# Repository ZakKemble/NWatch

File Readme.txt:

N|Watch - DIY Digital Wristwatch
http://blog.zakkemble.co.uk/diy-digital-wristwatch/

The firmware .hex and .eep files are compiled for ATmega328P

Fuses for ATmega328/328P
Internal RC 8MHz 6 CK/14CK + 65ms startup
Bootloader enabled, 256 words (512 bytes)
Serial program (SPI) enabled
Brown-out at 1.8V
High:		0xDE
Low:		0xE2
Extended:	0x06

./utils/bitmapConverter.exe
Utility to convert images (in ./imgs/) to pixel byte array

Font used for the large numbers on the main time display is AgencyFB Bold Wide available at http://www.fontsner.com/font/AgencyFBBoldWide-37966.html
My productions are published under GNU GPL v3 (see License.txt).

--------

Zak Kemble
contact@zakkemble.co.uk

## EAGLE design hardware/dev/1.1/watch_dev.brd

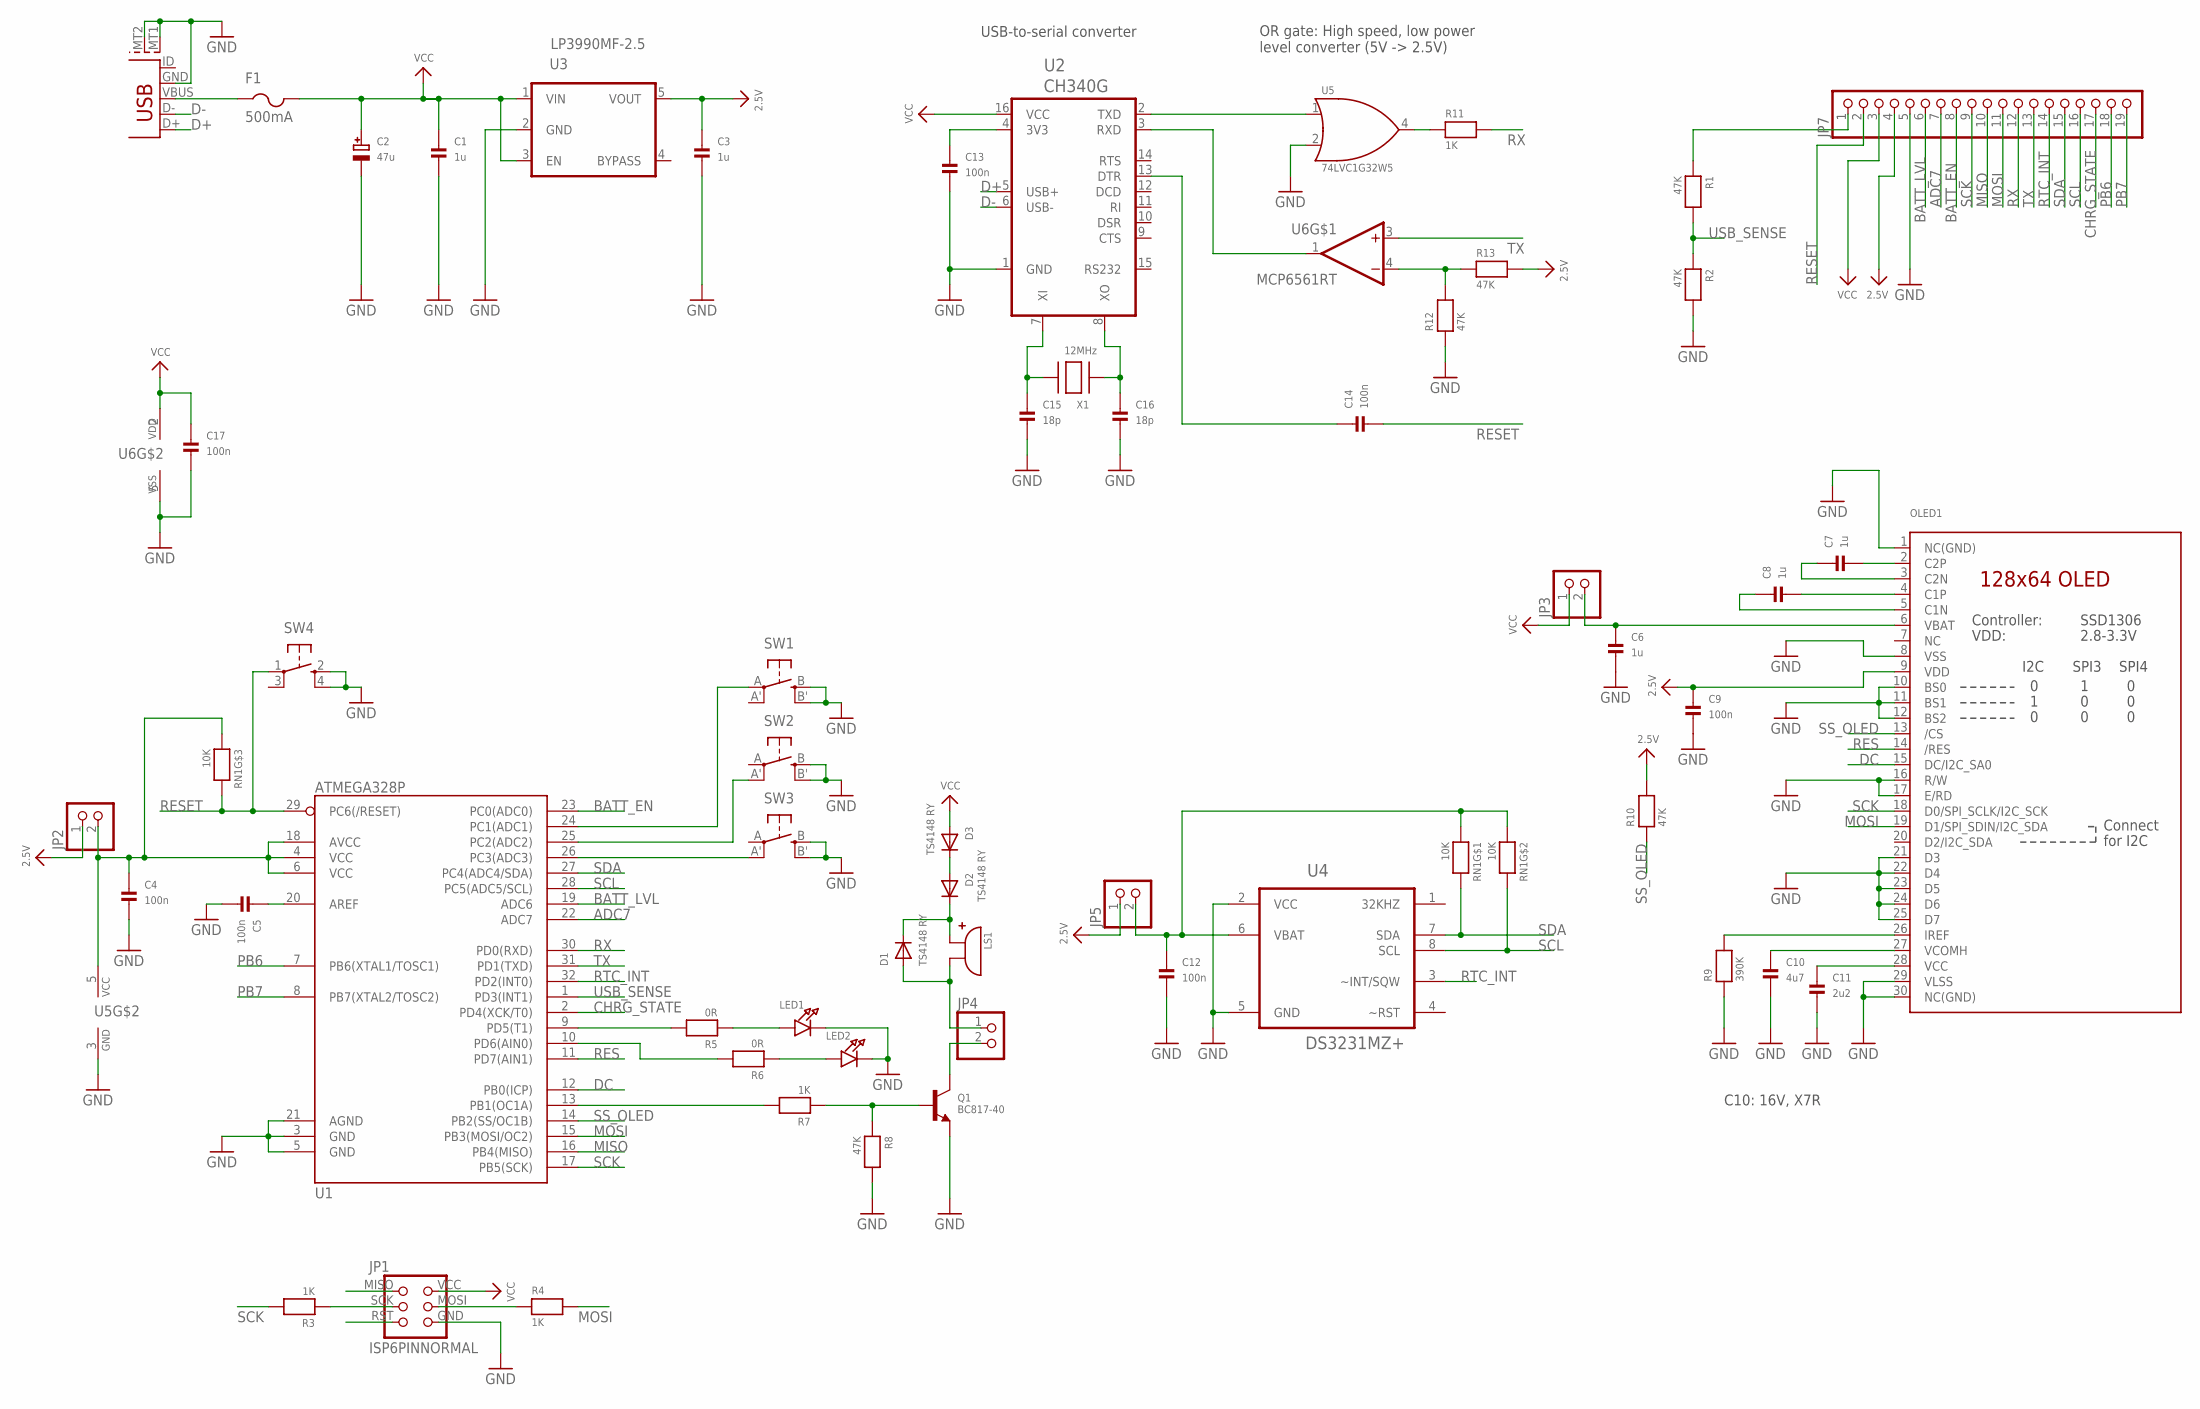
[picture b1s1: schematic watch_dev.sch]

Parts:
C1, C3, C6, C7, C8: 1u; 0805
C2: 47u; PANASONIC_C
C4, C5, C9, C12, C13, C14, C17: 100n; 0805
C10: 4u7; 0805
C11: 2u2; 0805
C15, C16: 18p; 0805
D1, D2, D3: TS4148 RY; 0805_DIODE
F1: 500mA; 1206
JP1: ISP6PINNORMAL; ISP6PIN
JP2, JP3, JP4, JP5: PINHD-1X2; 1X02
JP7: PINHD-1X19; 1X19
LED1, LED2: LED0805; CHIPLED_0805
LS1: ABMT-801-RC; PIEZO
OLED1: DISP_OLED_UG-2864HSWEG01_NOOUTLINE; UG-2864HSWEG01_1.3_WRAPAROUND
Q1: BC817-40; SOT23-WIDE
R1, R2, R8, R10, R12, R13: 47K; 0805
R3, R4, R7, R11: 1K; 0805
R5, R6: 0R; 0805
R9: 390K; 0805
RN1: 10K; RESPACK_4X0603
SW1, SW2, SW3: SPST_TACTMC32882; TACT_SMD4
SW4: SPST_TACTKMR2; KMR2
U1: ATMEGA328P; TQFP32-08
U2: CH340G; SOIC16_SMPAD
U3: LP3990MF-2.5; SOT95P275X110-5N
U4: DS3231MZ+; SOIC8_150MIL_SMPAD
U5: 74LVC1G32W5; SOT95P275X110-5N
U6: MCP6561RT; SOT95P275X110-5N
USB1: USB-MICROBLARGEPAD; USB-MICROB_LARGEPAD
X1: 12MHz; NX5032

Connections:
2.5V: C3.1, C9.1, JP2.1, JP5.1, JP7.4, OLED1.9 (VDD), R10.2, R13.2, U3.5 (VOUT)
ADC7: JP7.7, U1.22 (ADC7)
BATT_EN: JP7.8, U1.23 (PC0(ADC0))
BATT_LVL: JP7.6, U1.19 (ADC6)
CHRG_STATE: JP7.17, U1.2 (PD4(XCK/T0))
D+: U2.5 (USB+), USB1.D+
D-: U2.6 (USB-), USB1.D-
DC: OLED1.15 (DC/I2C_SA0), U1.12 (PB0(ICP))
GND: C1.2, C2.-, C3.2, C4.2, C5.2, C6.2, C9.2, C10.2, C11.2, C12.2, C13.2, C15.2, C16.2, C17.2, JP1.GND (6), JP7.5, LED1.C, LED2.C, OLED1.1 (NC(GND)), OLED1.8 (VSS), OLED1.10 (BS0), OLED1.11 (BS1), OLED1.12 (BS2), OLED1.16 (R/W), OLED1.17 (E/RD), OLED1.21 (D3), OLED1.22 (D4), OLED1.23 (D5), OLED1.24 (D6), OLED1.25 (D7), OLED1.29 (VLSS), OLED1.30 (NC(GND)), Q1.2 (E), R2.2, R8.2, R9.1, R12.1, SW1.B (S), SW1.B' (S1), SW2.B (S), SW2.B' (S1), SW3.B (S), SW3.B' (S1), SW4.2 (S), SW4.4 (S1), U1.3 (GND), U1.5 (GND), U1.21 (AGND), U2.1 (GND), U3.2 (GND), U4.2 (VCC), U4.5 (GND), U5.2 (B), U5.3 (GND), U6.5 (VSS), USB1.GND, USB1.MT1 (SHEILD1), USB1.MT2 (SHEILD2)
MISO: JP1.MISO (1), JP7.10, U1.16 (PB4(MISO))
MOSI: JP7.11, OLED1.19 (D1/SPI_SDIN/I2C_SDA), R4.2, U1.15 (PB3(MOSI/OC2))
unnamed: C5.1, U1.20 (AREF)
unnamed: SW1.A, U1.24 (PC1(ADC1))
unnamed: C7.2, OLED1.2 (C2P)
unnamed: SW3.A' (P1), U1.26 (PC3(ADC3))
unnamed: OLED1.26 (IREF), R9.2
unnamed: JP7.1, R1.1
unnamed: D1.1 (A), JP4.1, LS1.2 (GND)
unnamed: Q1.1 (B), R7.1, R8.1
unnamed: SW2.A' (P1), U1.25 (PC2(ADC2))
unnamed: F1.1, USB1.VBUS
unnamed: R5.2, U1.9 (PD5(T1))
unnamed: C6.1, JP3.2, OLED1.6 (VBAT)
unnamed: C8.1, OLED1.5 (C1N)
unnamed: C8.2, OLED1.4 (C1P)
unnamed: C7.1, OLED1.3 (C2N)
unnamed: R6.2, U1.10 (PD6(AIN0))
unnamed: C4.1, JP2.2, RN1.3 (1), U1.4 (VCC), U1.6 (VCC), U1.18 (AVCC), U5.5 (VCC)
unnamed: JP4.2, Q1.3 (C)
unnamed: C10.1, OLED1.27 (VCOMH)
unnamed: C11.1, OLED1.28 (VCC)
unnamed: C15.1, U2.7 (XI), X1.P$2
unnamed: JP1.SCK (3), R3.1
unnamed: C16.1, U2.8 (XO), X1.P$1
unnamed: JP1.MOSI (4), R4.1
unnamed: C13.1, U2.4 (3V3)
unnamed: U2.2 (TXD), U5.1 (A)
unnamed: R11.1, U5.4 (Y)
unnamed: LED1.A, R5.1
unnamed: LED2.A, R6.1
unnamed: C14.1, U2.13 (DTR)
unnamed: C12.1, JP5.2, RN1.1, RN1.2 (1), U4.6 (VBAT)
unnamed: D1.2 (C), D2.2 (C), LS1.1 (VCC)
unnamed: D2.1 (A), D3.2 (C)
unnamed: U2.3 (RXD), U6.1 (OUT)
unnamed: R12.2, R13.1, U6.4 (-IN)
PB6: JP7.18, U1.7 (PB6(XTAL1/TOSC1))
PB7: JP7.19, U1.8 (PB7(XTAL2/TOSC2))
PIEZO: R7.2, U1.13 (PB1(OC1A))
RES: OLED1.14 (/RES), U1.11 (PD7(AIN1))
RESET: C14.2, JP1.RST (5), JP7.2, RN1.6 (2), SW4.1, U1.29 (PC6(/RESET))
RTC_INT: JP7.14, U1.32 (PD2(INT0)), U4.3 (~INT/SQW)
RX: JP7.12, R11.2, U1.30 (PD0(RXD))
SCK: JP7.9, OLED1.18 (D0/SPI_SCLK/I2C_SCK), R3.2, U1.17 (PB5(SCK))
SCL: JP7.16, RN1.7 (2), U1.28 (PC5(ADC5/SCL)), U4.8 (SCL)
SDA: JP7.15, RN1.8 (2), U1.27 (PC4(ADC4/SDA)), U4.7 (SDA)
SS_OLED: OLED1.13 (/CS), R10.1, U1.14 (PB2(SS/OC1B))
TX: JP7.13, U1.31 (PD1(TXD)), U6.3 (+IN)
USB_SENSE: R1.2, R2.1, U1.1 (PD3(INT1))
VCC: C1.1, C2.+, C17.1, D3.1 (A), F1.2, JP1.VCC (2), JP3.1, JP7.3, U2.16 (VCC), U3.1 (VIN), U3.3 (EN), U6.2 (VDD)

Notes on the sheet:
C10: 16V, X7R
USB-to-serial converter
OR gate: High speed, low power level converter (5V -> 2.5V)

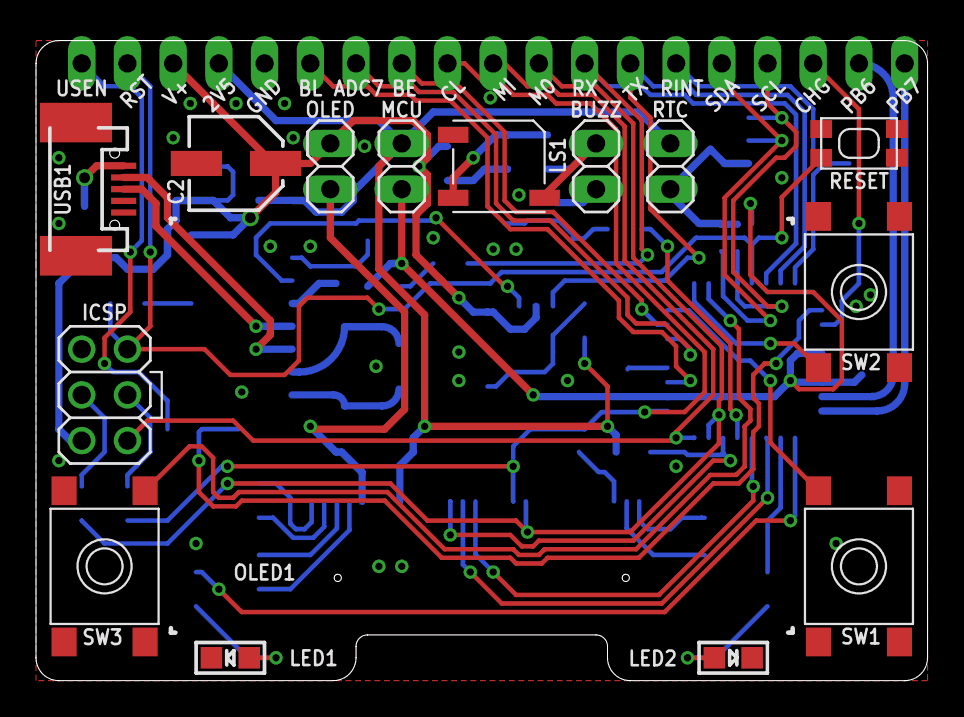
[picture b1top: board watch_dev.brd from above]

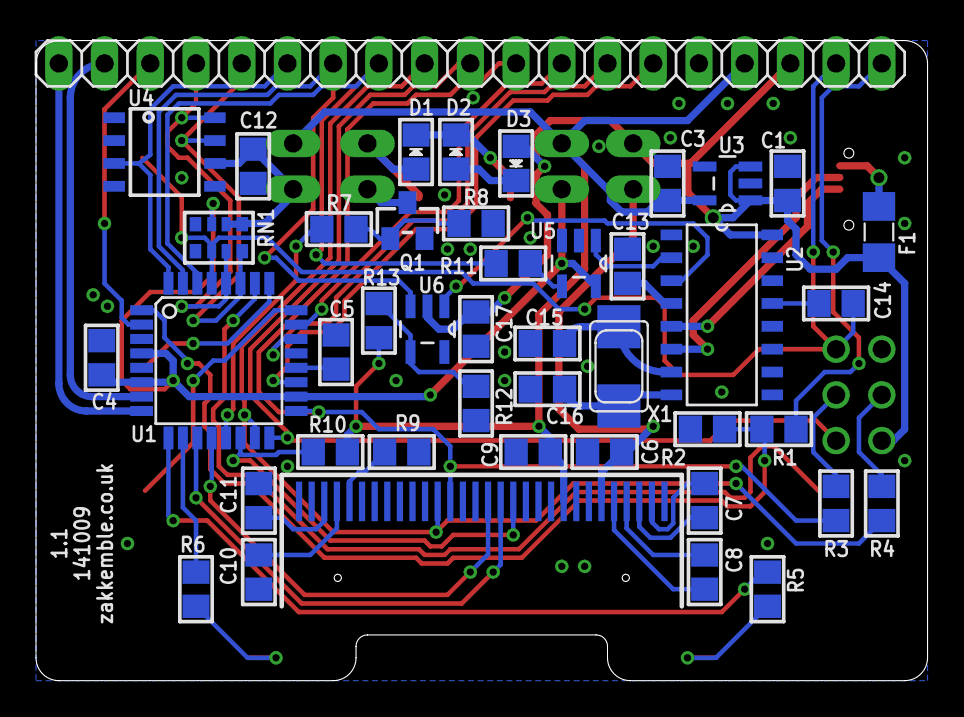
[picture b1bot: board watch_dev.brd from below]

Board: 2 copper layers, 49.5 x 35.6 mm, 58 parts (43 on the bottom side), 60 nets.

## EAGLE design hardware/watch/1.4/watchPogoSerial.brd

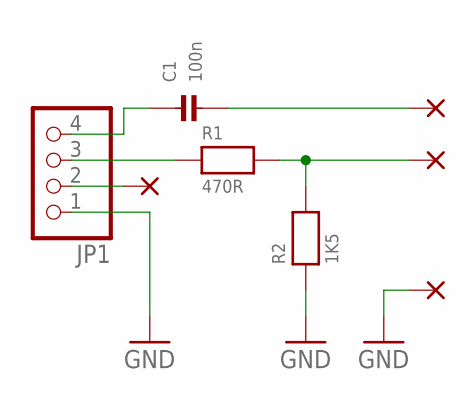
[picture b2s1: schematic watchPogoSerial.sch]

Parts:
C1: 100n; 0805
JP1: PINHD-1X4; 1X04
PAD1, PAD3, PAD6, PAD12: PAD0.8-LRG; PAD-0.8-LRG
R1: 470R; 0805
R2: 1K5; 0805

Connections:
GND: JP1.1, PAD1.P$1, R2.1
unnamed: C1.1, JP1.4
unnamed: C1.2, PAD3.P$1
unnamed: JP1.3, R1.1
unnamed: PAD6.P$1, R1.2, R2.2
unnamed: JP1.2, PAD12.P$1

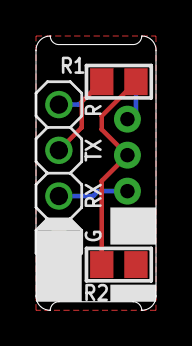
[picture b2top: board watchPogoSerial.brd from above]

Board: 2 copper layers, 6.7 x 15.2 mm, 8 parts (1 on the bottom side), 6 nets.

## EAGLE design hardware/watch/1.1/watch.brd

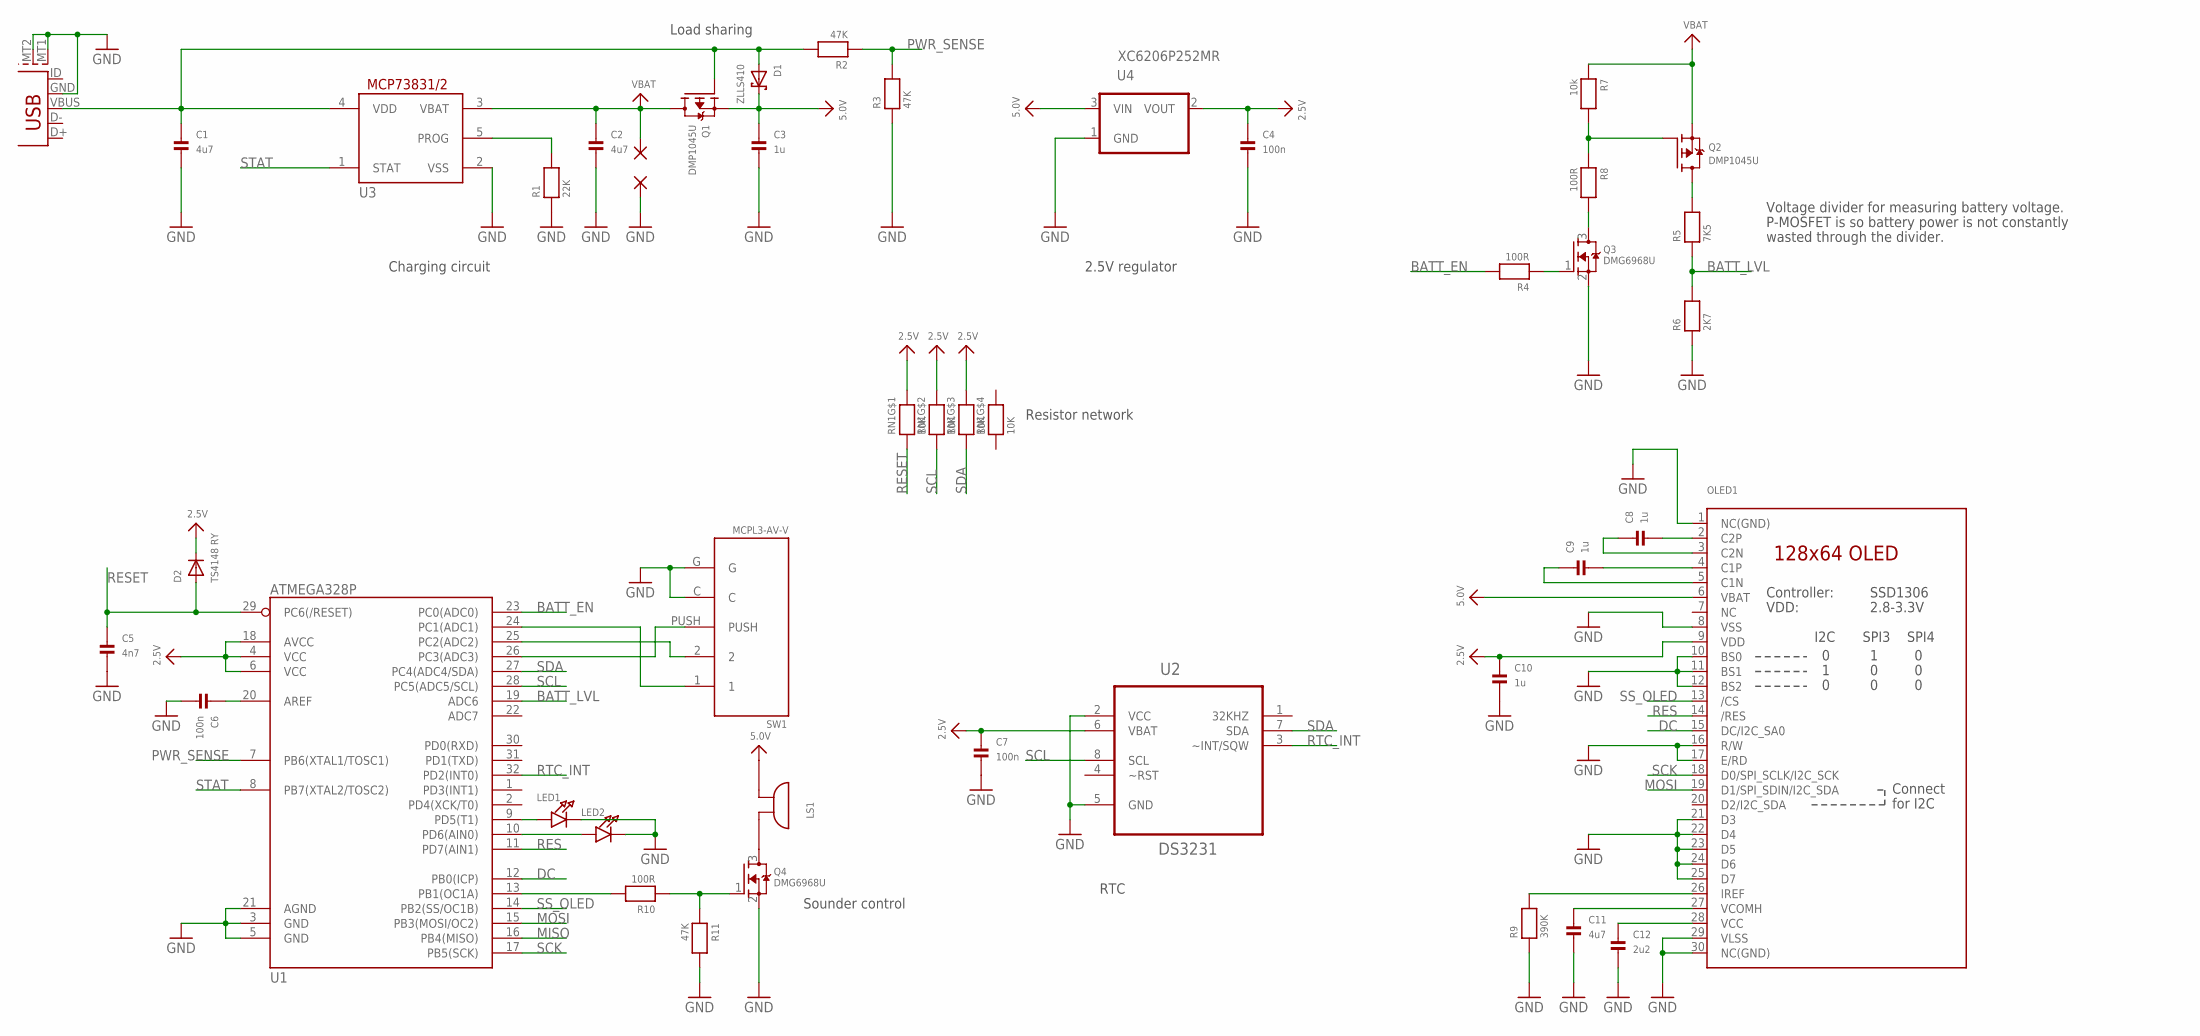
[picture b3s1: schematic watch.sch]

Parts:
C1, C2, C11: 4u7; 0805
C3, C8, C9, C10: 1u; 0805
C4, C6, C7: 100n; 0805
C5: 4n7; 0805
C12: 2u2; 0805
D1: ZLLS410; SOD-323
D2: TS4148 RY; DIODE0805
LED1, LED2: LED0805; CHIPLED_0805
LS1: ABMT-801-RC; PIEZO
OLED1: DISP_OLED_UG-2864HSWEG01_NOOUTLINE; UG-2864HSWEG01_1.3_WRAPAROUND
PAD1, PAD2: SMD2; SMD1,27-2,54
Q1, Q2: DMP1045U; SOT23-WIDE
Q3, Q4: DMG6968U; SOT23-WIDE
R1: 22K; 0805
R2, R3: 47K; 0805_NOTHERMALS
R4, R8, R10: 100R; 0805
R5: 7K5; 0805
R6: 2K7; 0805
R7: 10k; 0805
R9: 390K; 0805
R11: 47K; 0805
RN1: 10K; RESPACK_4X0603
SW1: MCPL3-AV-V; MCPL3-AC-V
U1: ATMEGA328P; TQFP32-08
U2: DS3231; SOIC8_150MIL
U3: MCP73832T-2ACI/OT; SOT23-5L
U4: XC6206P252MR; SOT-23
USB1: USB-MICROBLARGEPAD; USB-MICROB_LARGEPAD

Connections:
2.5V: C4.1, C7.1, C10.1, D2.2 (C), OLED1.9 (VDD), RN1.6 (2), RN1.7 (2), RN1.8 (2), U1.4 (VCC), U1.6 (VCC), U1.18 (AVCC), U2.6 (VBAT), U4.2 (VOUT)
5.0V: C3.1, D1.C, LS1.1 (VCC), OLED1.6 (VBAT), Q1.2 (S), U4.3 (VIN)
BATT_EN: R4.2, U1.23 (PC0(ADC0))
BATT_LVL: R5.1, R6.2, U1.19 (ADC6)
DC: OLED1.15 (DC/I2C_SA0), U1.12 (PB0(ICP))
GND: C1.2, C2.2, C3.2, C4.2, C5.2, C6.2, C7.2, C10.2, C11.2, C12.2, LED1.C, LED2.C, OLED1.1 (NC(GND)), OLED1.8 (VSS), OLED1.10 (BS0), OLED1.11 (BS1), OLED1.12 (BS2), OLED1.16 (R/W), OLED1.17 (E/RD), OLED1.21 (D3), OLED1.22 (D4), OLED1.23 (D5), OLED1.24 (D6), OLED1.25 (D7), OLED1.29 (VLSS), OLED1.30 (NC(GND)), PAD2.1, Q3.2 (S), Q4.2 (S), R1.1, R3.1, R6.1, R9.1, R11.2, SW1.C, SW1.G, U1.3 (GND), U1.5 (GND), U1.21 (AGND), U2.2 (VCC), U2.5 (GND), U3.2 (VSS), U4.1 (GND), USB1.GND, USB1.MT1 (SHEILD1), USB1.MT2 (SHEILD2)
MISO: U1.16 (PB4(MISO))
MOSI: OLED1.19 (D1/SPI_SDIN/I2C_SDA), U1.15 (PB3(MOSI/OC2))
unnamed: C6.1, U1.20 (AREF)
unnamed: SW1.1, U1.24 (PC1(ADC1))
unnamed: C8.2, OLED1.2 (C2P)
unnamed: SW1.2, U1.25 (PC2(ADC2))
unnamed: OLED1.26 (IREF), R9.2
unnamed: C1.1, D1.A, Q1.1 (G), R2.2, U3.4 (VDD), USB1.VBUS
unnamed: LS1.2 (GND), Q4.3 (D)
unnamed: Q4.1 (G), R10.1, R11.1
unnamed: SW1.PUSH, U1.26 (PC3(ADC3))
unnamed: R1.2, U3.5 (PROG)
unnamed: LED1.A, U1.9 (PD5(T1))
unnamed: Q2.1 (G), R7.2, R8.1
unnamed: C9.1, OLED1.5 (C1N)
unnamed: C9.2, OLED1.4 (C1P)
unnamed: C8.1, OLED1.3 (C2N)
unnamed: LED2.A, U1.10 (PD6(AIN0))
unnamed: Q3.3 (D), R8.2
unnamed: Q2.3 (D), R5.2
unnamed: C11.1, OLED1.27 (VCOMH)
unnamed: C12.1, OLED1.28 (VCC)
unnamed: Q3.1 (G), R4.1
PIEZO: R10.2, U1.13 (PB1(OC1A))
PWR_SENSE: R2.1, R3.2, U1.7 (PB6(XTAL1/TOSC1))
RES: OLED1.14 (/RES), U1.11 (PD7(AIN1))
RESET: C5.1, D2.1 (A), RN1.1, U1.29 (PC6(/RESET))
RTC_INT: U1.32 (PD2(INT0)), U2.3 (~INT/SQW)
SCK: OLED1.18 (D0/SPI_SCLK/I2C_SCK), U1.17 (PB5(SCK))
SCL: RN1.2 (1), U1.28 (PC5(ADC5/SCL)), U2.8 (SCL)
SDA: RN1.3 (1), U1.27 (PC4(ADC4/SDA)), U2.7 (SDA)
SS_OLED: OLED1.13 (/CS), U1.14 (PB2(SS/OC1B))
STAT: U1.8 (PB7(XTAL2/TOSC2)), U3.1 (STAT)
VBAT: C2.1, PAD1.1, Q1.3 (D), Q2.2 (S), R7.1, U3.3 (VBAT)

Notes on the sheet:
Charging circuit
Resistor network
2.5V regulator
Voltage divider for measuring battery voltage.
RTC
Load sharing
P-MOSFET is so battery power is not constantly
wasted through the divider.
Sounder control

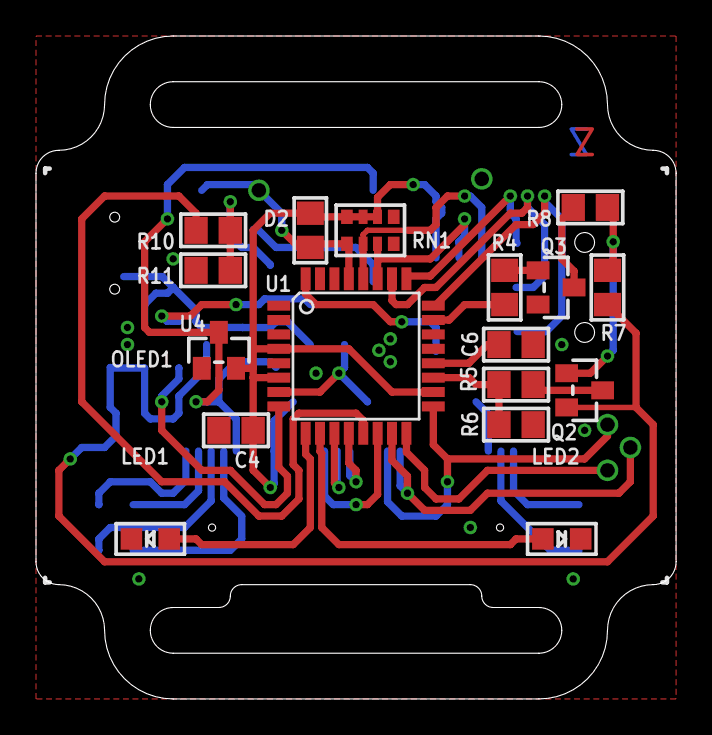
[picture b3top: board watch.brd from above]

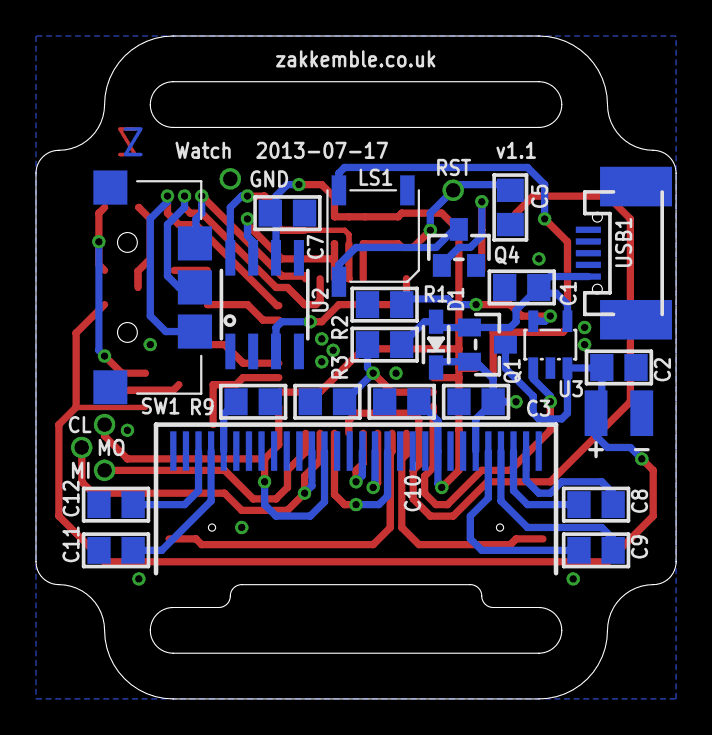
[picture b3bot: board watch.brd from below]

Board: 2 copper layers, 35.6 x 36.8 mm, 42 parts (24 on the bottom side), 39 nets.

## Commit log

2014-06-28 Lots of stuff
    Software:
    - Added a bootloader (slightly modified Optiboot, added support for
    ATmega328 non-P and reading/writing EEPROM)
    - Reduced flash and RAM usage (Flash: 29156 -> 26702 (2454), RAM: 1407
    -> 1300 (107))
    - Added support for playing tunes
2014-06-28 Some more stuff
    Forgot to commit some files
2014-06-30 Fixed tune priority not resetting
    Also added new lines to end of files
2014-07-01 Schematic adjustments
    D1 was ZLLS410, should be BAT60JFILM
2014-10-13 Hardware updated
    N|Watch (v1.4):
    - Q2, Q3, Q4 MOSFETs changed to BJTs (BC817-40 & BC807-40)
    - R2, R3 100R gate resistors changed to 47K and 1K
    - R4 has been removed (now all resistors in RN3 are being using)
2014-10-13 Added early battery undervoltage cutoff
    - Added early battery undervoltage cutoff. Improves battery lifespan by
    not letting the voltage go so low and the RTC will continue working
    since the battery's own PCM hasn't kicked in yet
    - Slightly reduced power consumption by going into power save sleep
    instead of idle sleep if no other peripherals are in use
    - Various code optimisations
2014-10-15 Added images for the wiki
2014-10-20 Fixed alarm bug
2014-10-29 12 hour mode, Russian translation
    Added 12 hour time option
    Russian translation, thanks to Onatsky Sergei (Le_Fleurs (-at-) mail
    (-dot-) ru)
    Bootloader baud changed from 76800 to 57600 (Linux doesn't like 76800)
2014-11-08 Updated Russian translation & added N|WatchDev
    Updated Russian translation (day of week images)
    Released N|WatchDev designs (dev board version of the watch)
2014-11-15 Fixed issue for when RTC isn't connected
2015-01-10 Code cleanup
    Got rid of the images_s struct stuff for drawing bitmaps, back to the
    normal way of calling draw_bitmap(...). It was an experiment to see if
    it produced faster/smaller code when passing a pointer to a struct with
    all the data instead of a bunch of func args. Ended up with the code
    being slightly slower and larger.
2015-04-03 Added support for SH1106 OLEDs
    See OLED_CONTROLLER in config.h
2015-10-05 Removed some pretty pointless code

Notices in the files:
parts and their libraries:
microbuilder: This work is placed in the public domain, and may be freely used for commercial and non-commercial work with the following conditions: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
SparkFun-DigitalIC: Licensing: CC v3.0 Share-Alike You are welcome to use this library for commercial purposes.
